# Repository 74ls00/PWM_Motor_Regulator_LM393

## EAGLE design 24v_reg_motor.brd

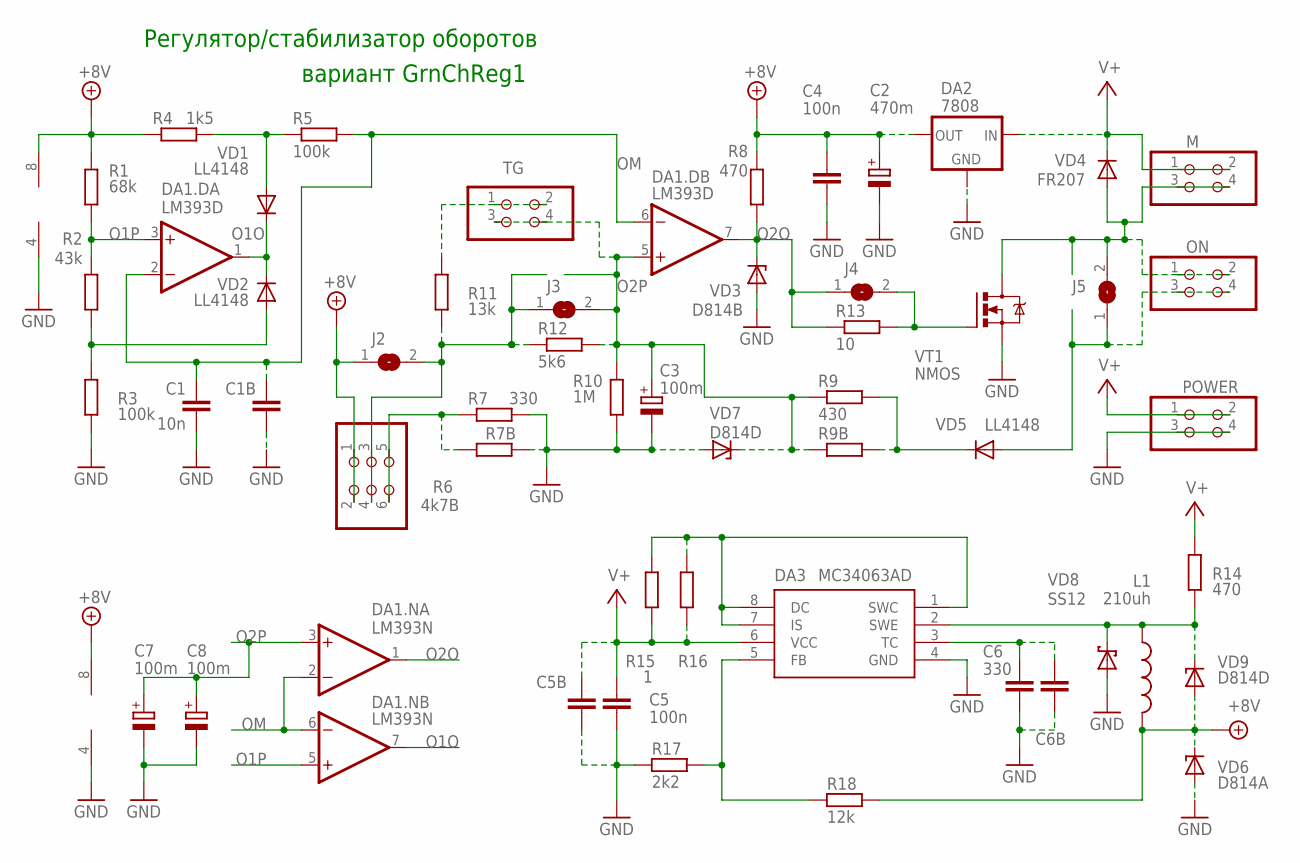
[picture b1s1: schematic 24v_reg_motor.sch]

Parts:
C1: 10n; C025-025X050
C1B, C6B: C-EUC0805; C0805
C2: 470m; E5-8,5
C3: 100m; E2,5-7
C4: 100n; C1206K
C5: 100n; C025-024X044
C5B: C-EUC1206; C1206
C6: 330; C025-025X050
C7, C8: 100m; E22-6
DA1.D: LM393D; SO08
DA1.N: LM393N; DIL08
DA2: 7808; 79XXL
DA3: MC34063AD; SOIC8
J2, J3, J4, J5: SJ
L1: 210uh; 0207/10
M: PINHD-2X2; 2X02
ON: PINHD-2X2; 2X02
POWER: PINHD-2X2; 2X02
R1: 68k; 0207/10
R2: 43k; M0805
R3, R5: 100k; M0805
R4: 1k5; M0805
R6: 4k7B; 2X03
R7: 330; 0309/10
R7B, R16: R-EU_M0805; M0805
R8: 470; M0805
R9: 430; 0207/10
R9B: R-EU_R0805; R0805
R10: 1M; M0805
R11: 13k; 0207/10
R12: 5k6; M0805
R13: 10; R0805
R14: 470; 0207/10
R15: 1; M0805
R17: 2k2; M0805
R18: 12k; 0207/10
TG: PINHD-2X2; 2X02
VD1, VD2, VD5: LL4148; SOD80C
VD3: D814B; ZDMETAL
VD4: FR207; DO35-10
VD6: D814A; ZDMETAL
VD7, VD9: D814D; ZDMETAL
VD8: SS12; SMB
VT1: NMOS; DPACK_1

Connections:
34P2: DA3.2 (SWE), L1.1, R14.2, VD8.C, VD9.C
+8V: C2.+, C4.1, DA1.D.8 (V+), DA1.N.8 (V+), DA2.OUT, J2.1, L1.2, R1.2, R4.1, R6.1, R6.2, R8.2, R18.2, VD6.C, VD9.A
GND: C1.2, C1B.2, C2.-, C3.-, C4.2, C5.2, C5B.2, C6.2, C6B.2, C7.-, C8.-, DA1.D.4 (V-), DA1.N.4 (V-), DA2.GND, DA3.4 (GND), POWER.3, POWER.4, R3.1, R7.1, R7B.1, R10.1, R17.1, VD3.A, VD6.A, VD7.A, VD8.A, VT1.S
unnamed: R2.1, R3.2, VD2.A
unnamed: R4.2, R5.1, VD1.A
unnamed: R6.5, R6.6, R7.2, R7B.2
unnamed: DA3.1 (SWC), DA3.7 (IS), DA3.8 (DC), R15.2, R16.2
unnamed: J5.2, M.3, M.4, ON.1, ON.2, VD4.A, VT1.D
unnamed: J4.2, R13.2, VT1.G
unnamed: R11.2, TG.1, TG.2
unnamed: J5.1, ON.3, ON.4, VD5.A
unnamed: R9.2, R9B.2, VD5.C
unnamed: J2.2, J3.1, R6.3, R6.4, R11.1, R12.1
unnamed: DA3.5 (FB), R17.2, R18.1
unnamed: C6.1, C6B.1, DA3.3 (TC)
O1O: DA1.D.1 (OUT), DA1.N.7 (OUT), VD1.C, VD2.C
O1P: DA1.D.3 (+IN), DA1.N.5 (+IN), R1.1, R2.2
O2O: DA1.D.7 (OUT), DA1.N.1 (OUT), J4.1, R8.1, R13.1, VD3.C
O2P: C3.+, C7.+, C8.+, DA1.D.5 (+IN), DA1.N.3 (+IN), J3.2, R9.1, R9B.1, R10.2, R12.2, TG.3, TG.4, VD7.C
OM: C1.1, C1B.1, DA1.D.2 (-IN), DA1.D.6 (-IN), DA1.N.2 (-IN), DA1.N.6 (-IN), R5.2
V+: C5.1, C5B.1, DA2.IN, DA3.6 (VCC), M.1, M.2, POWER.1, POWER.2, R14.1, R15.1, R16.1, VD4.C

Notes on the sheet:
Регулятор/стабилизатор оборотов
вариант GrnChReg1

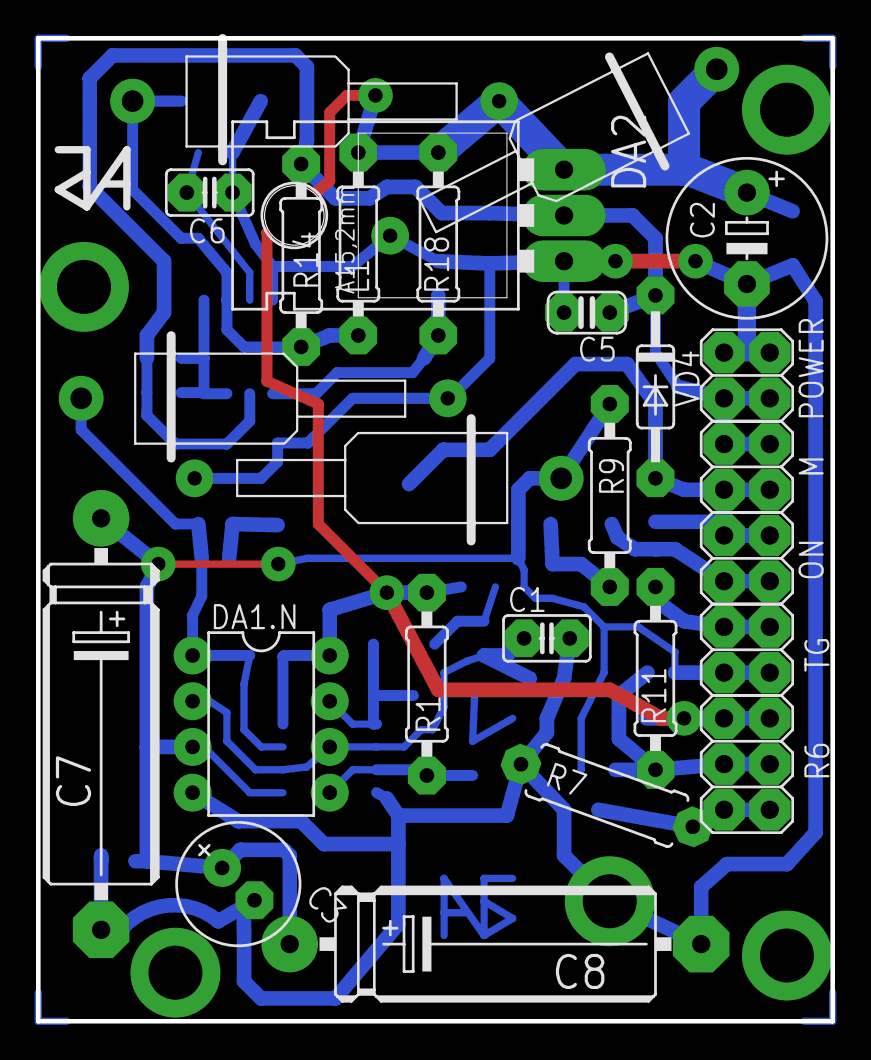
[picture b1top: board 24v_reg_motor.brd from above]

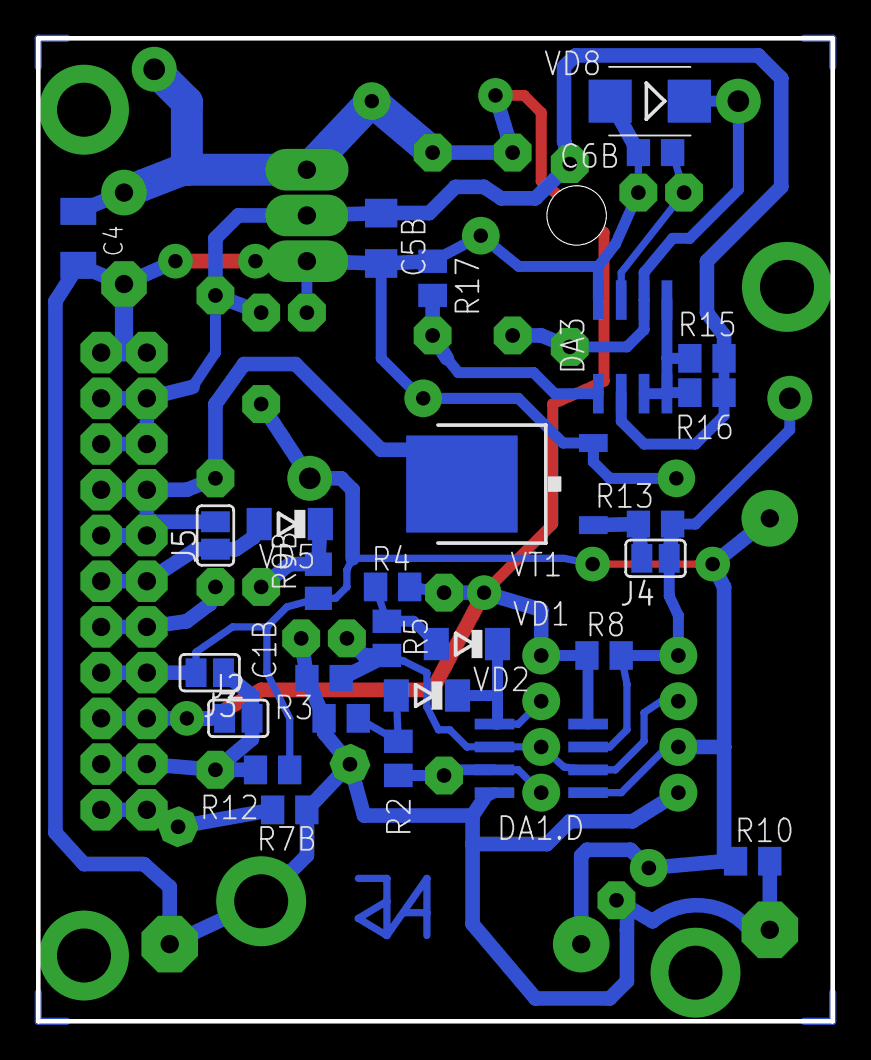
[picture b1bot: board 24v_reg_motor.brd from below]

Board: 2 copper layers, 44.1 x 54.6 mm, 54 parts (28 on the bottom side), 21 nets.
